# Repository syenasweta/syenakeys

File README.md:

# SyenaKeys

Mechanical keyboards by Syenasweta a.k.a. Nashrullah Ali Fauzi.

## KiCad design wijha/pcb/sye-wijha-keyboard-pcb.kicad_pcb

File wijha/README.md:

# SYE-Wijha
Mechanical keyboards with six switch for mouse and arrow keys.

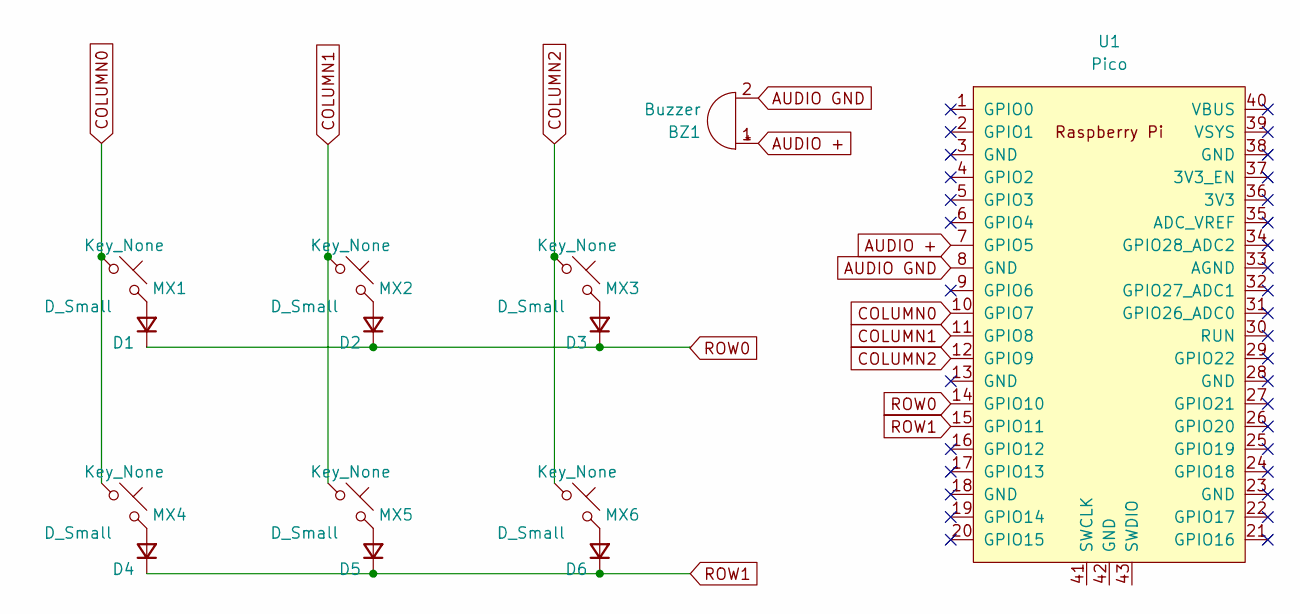
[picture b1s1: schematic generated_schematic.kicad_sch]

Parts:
BZ1: Buzzer; MagneticBuzzer_PUI_AT-0927-TT-6-R
D1, D2, D3, D4, D5, D6: D_Small; D_DO-35_SOD27_P7.62mm_Horizontal
MX1, MX2, MX3, MX4, MX5, MX6: Key_None; SW_MX_HS_CPG151101S11_1u
U1: Pico; RPi_Pico_SMD_TH

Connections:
AUDIO +: BZ1.1 (+), U1.7 (GPIO5)
AUDIO GND: BZ1.2 (-), U1.8 (GND)
COLUMN0: MX1.1, MX4.1, U1.10 (GPIO7)
COLUMN1: MX2.1, MX5.1, U1.11 (GPIO8)
COLUMN2: MX3.1, MX6.1, U1.12 (GPIO9)
unnamed: D1.2 (A), MX1.2
unnamed: D2.2 (A), MX2.2
unnamed: D3.2 (A), MX3.2
unnamed: D4.2 (A), MX4.2
unnamed: D5.2 (A), MX5.2
unnamed: D6.2 (A), MX6.2
ROW0: D1.1 (K), D2.1 (K), D3.1 (K), U1.14 (GPIO10)
ROW1: D4.1 (K), D5.1 (K), D6.1 (K), U1.15 (GPIO11)

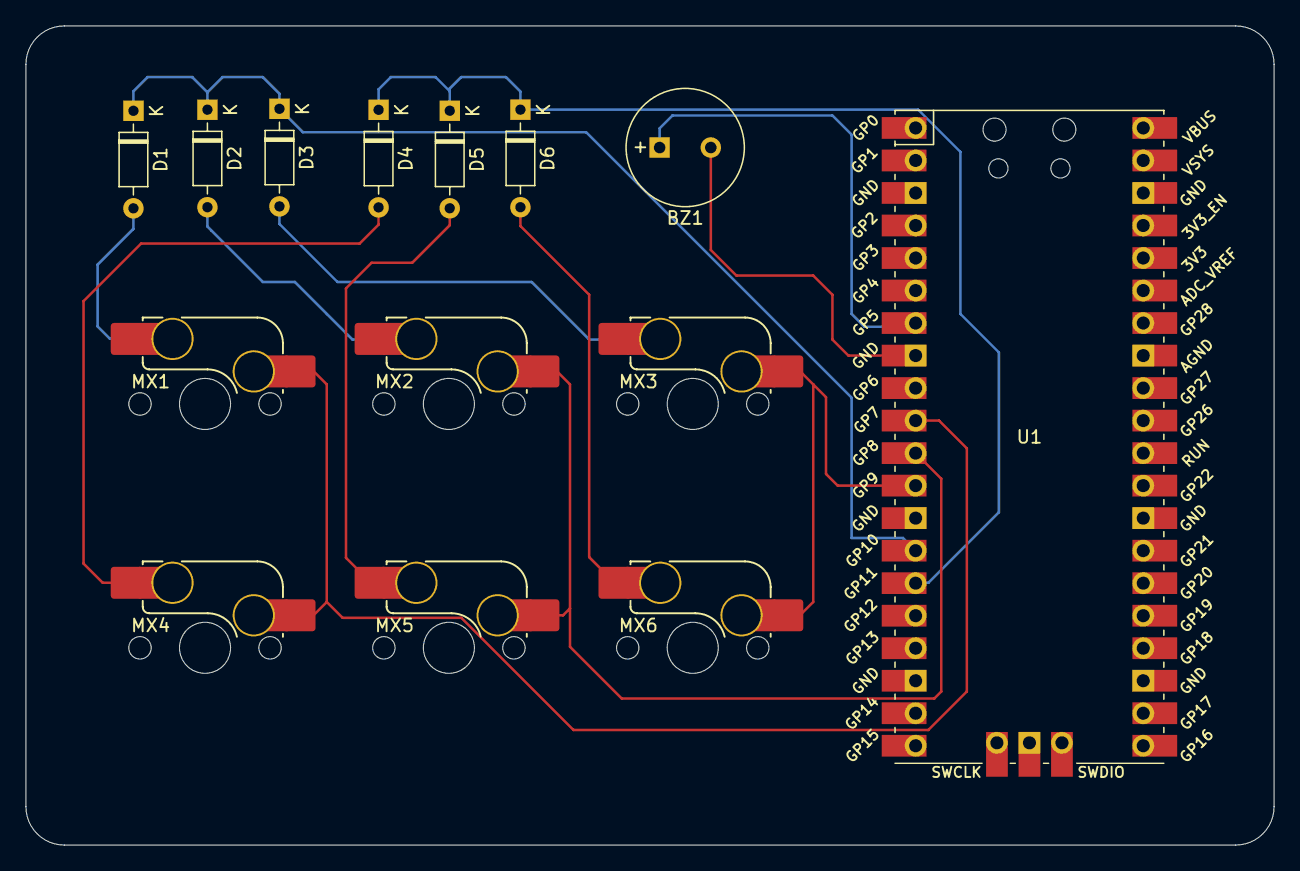
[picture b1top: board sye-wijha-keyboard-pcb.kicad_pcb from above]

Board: 2 copper layers, 97.5 x 64.0 mm, 14 parts (0 on the bottom side), 13 nets.
